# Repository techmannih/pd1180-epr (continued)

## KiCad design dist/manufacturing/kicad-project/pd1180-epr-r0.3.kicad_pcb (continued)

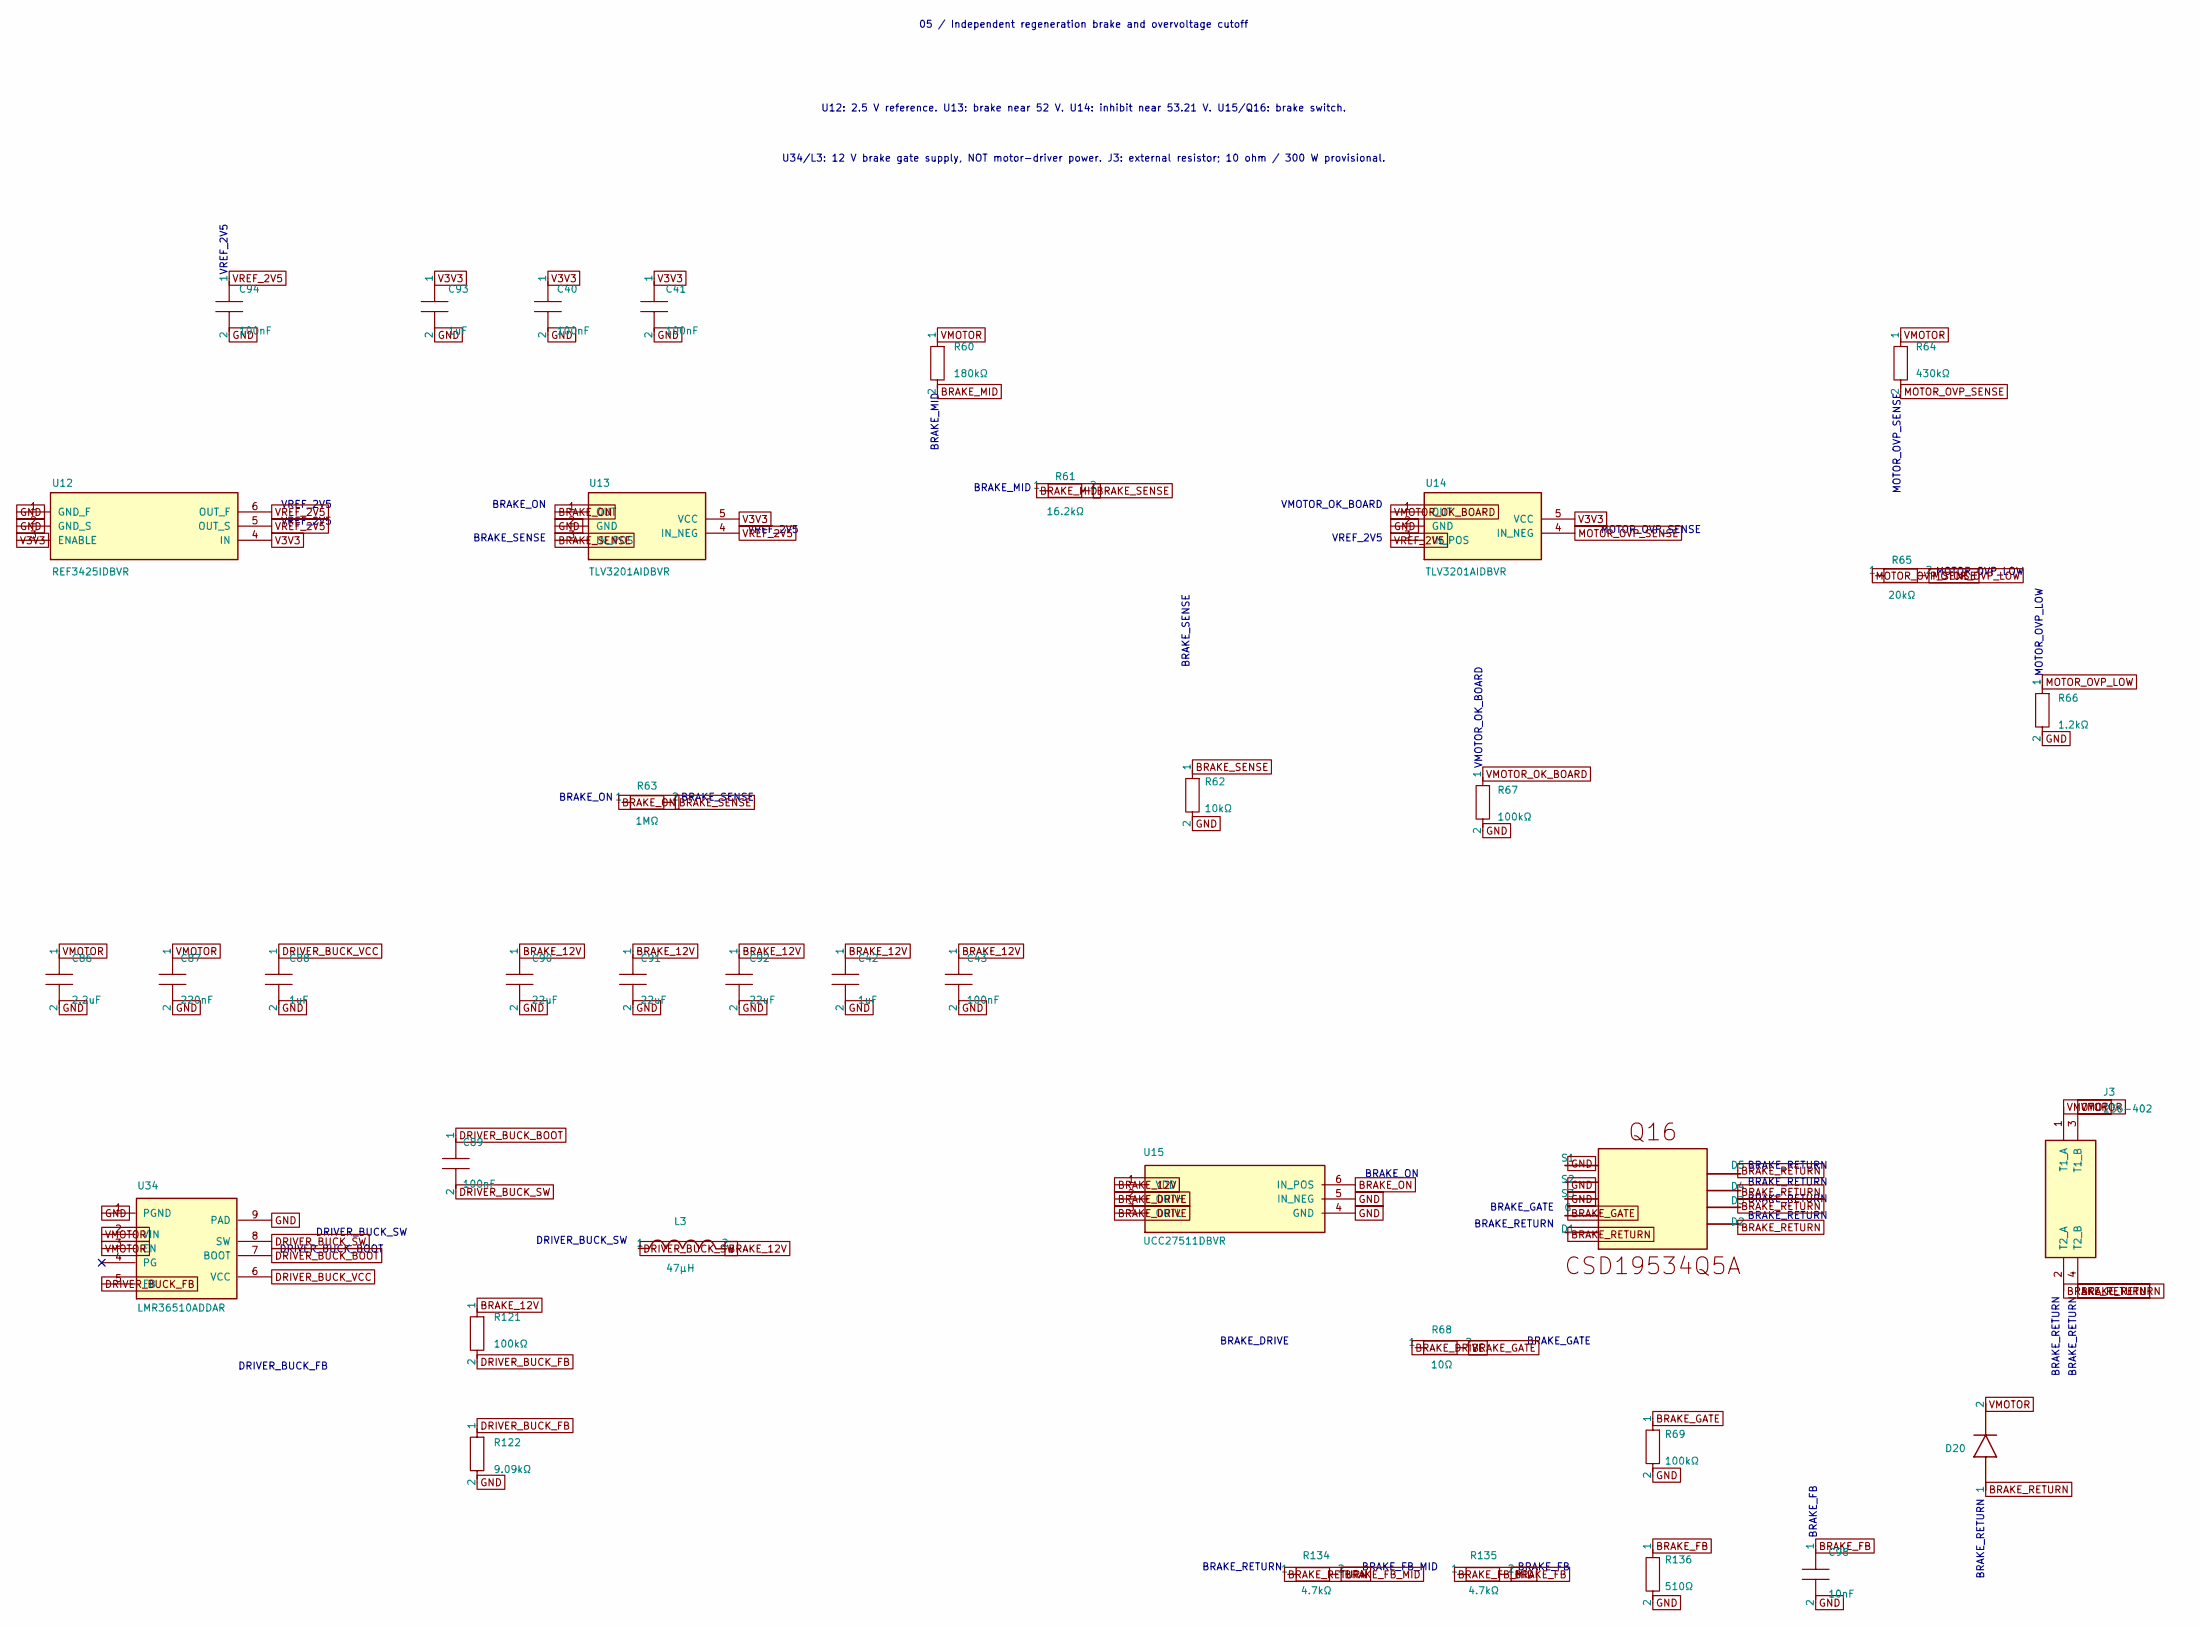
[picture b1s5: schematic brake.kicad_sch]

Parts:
C40, C41, C43, C89, C94: 100nF; capacitor_cap0603
C42, C88, C93: 1uF; capacitor_cap0603
C86: 2.2uF; capacitor_cap1206
C87: 220nF; capacitor_cap0805
C90, C91, C92: 22uF; capacitor_cap0805
C98: 10nF; capacitor_cap0603
D20: D; SS10100
J3: 236-402
L3: 47µH; SRP7050TA-470M
Q16: CSD19534Q5A
R60: 180kΩ; resistor_res0805
R61: 16.2kΩ; resistor_res0603
R62: 10kΩ; resistor_res0603
R63: 1MΩ; resistor_res0603
R64: 430kΩ; resistor_res0603
R65: 20kΩ; resistor_res0603
R66: 1.2kΩ; resistor_res0603
R67, R69, R121: 100kΩ; resistor_res0603
R68: 10Ω; resistor_res0603
R122: 9.09kΩ; resistor_res0603
R134, R135: 4.7kΩ; resistor_res1206
R136: 510Ω; resistor_res0603
U12: REF3425IDBVR
U13, U14: TLV3201AIDBVR
U15: UCC27511DBVR
U34: LMR36510ADDAR

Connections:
BRAKE_12V: C42.1, C43.1, C90.1, C91.1, C92.1, L3.2, R121.1, U15.1 (VDD)
BRAKE_DRIVE: R68.1, U15.2 (OUTH), U15.3 (OUTL)
BRAKE_FB: C98.1, R135.2, R136.1; also elsewhere on the board
BRAKE_FB_MID: R134.2, R135.1
BRAKE_GATE: Q16.4 (G), R68.2, R69.1
BRAKE_MID: R60.2, R61.1
BRAKE_ON: R63.1, U13.1 (OUT), U15.6 (IN_POS)
BRAKE_RETURN: D20.2 (1), J3.2 (T2_A), J3.4 (T2_B), Q16.5 (D1), Q16.6 (D2), Q16.7 (D3), Q16.8 (D4), Q16.9 (D5), R134.1
BRAKE_SENSE: R61.2, R62.1, R63.2, U13.3 (IN_POS)
DRIVER_BUCK_BOOT: C89.1, U34.7 (BOOT)
DRIVER_BUCK_FB: R121.2, R122.1, U34.5 (FB)
DRIVER_BUCK_SW: C89.2, L3.1, U34.8 (SW)
DRIVER_BUCK_VCC: C88.1, U34.6 (VCC)
GND: C40.2, C41.2, C42.2, C43.2, C86.2, C87.2, C88.2, C90.2, C91.2, C92.2, C93.2, C94.2, C98.2, Q16.1 (S1), Q16.2 (S2), Q16.3 (S3), R62.2, R66.2, R67.2, R69.2, R122.2, R136.2, U12.1 (GND_F), U12.2 (GND_S), U13.2 (GND), U14.2 (GND), U15.4 (GND), U15.5 (IN_NEG), U34.1 (PGND), U34.9 (PAD); also elsewhere on the board
MOTOR_OVP_LOW: R65.2, R66.1
MOTOR_OVP_SENSE: R64.2, R65.1, U14.4 (IN_NEG)
V3V3: C40.1, C41.1, C93.1, U12.3 (ENABLE), U12.4 (IN), U13.5 (VCC), U14.5 (VCC); also elsewhere on the board
VMOTOR: C86.1, C87.1, D20.1 (2), J3.1 (T1_A), J3.3 (T1_B), R60.1, R64.1, U34.2 (VIN), U34.3 (EN); also elsewhere on the board
VMOTOR_OK_BOARD: R67.1, U14.1 (OUT); also elsewhere on the board
VREF_2V5: C94.1, U12.5 (OUT_S), U12.6 (OUT_F), U13.4 (IN_NEG), U14.3 (IN_POS)

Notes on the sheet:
05 / Independent regeneration brake and overvoltage cutoff
U12: 2.5 V reference. U13: brake near 52 V. U14: inhibit near 53.21 V. U15/Q16: brake switch.
U34/L3: 12 V brake gate supply, NOT motor-driver power. J3: external resistor; 10 ohm / 300 W provisional.
DRIVER_BUCK_FB
DRIVER_BUCK_SW
VREF_2V5
BRAKE_ON
BRAKE_SENSE
MOTOR_OVP_SENSE
BRAKE_DRIVE
BRAKE_GATE
BRAKE_RETURN
BRAKE_FB
DRIVER_BUCK_BOOT
BRAKE_MID
VMOTOR_OK_BOARD
MOTOR_OVP_LOW
BRAKE_FB_MID

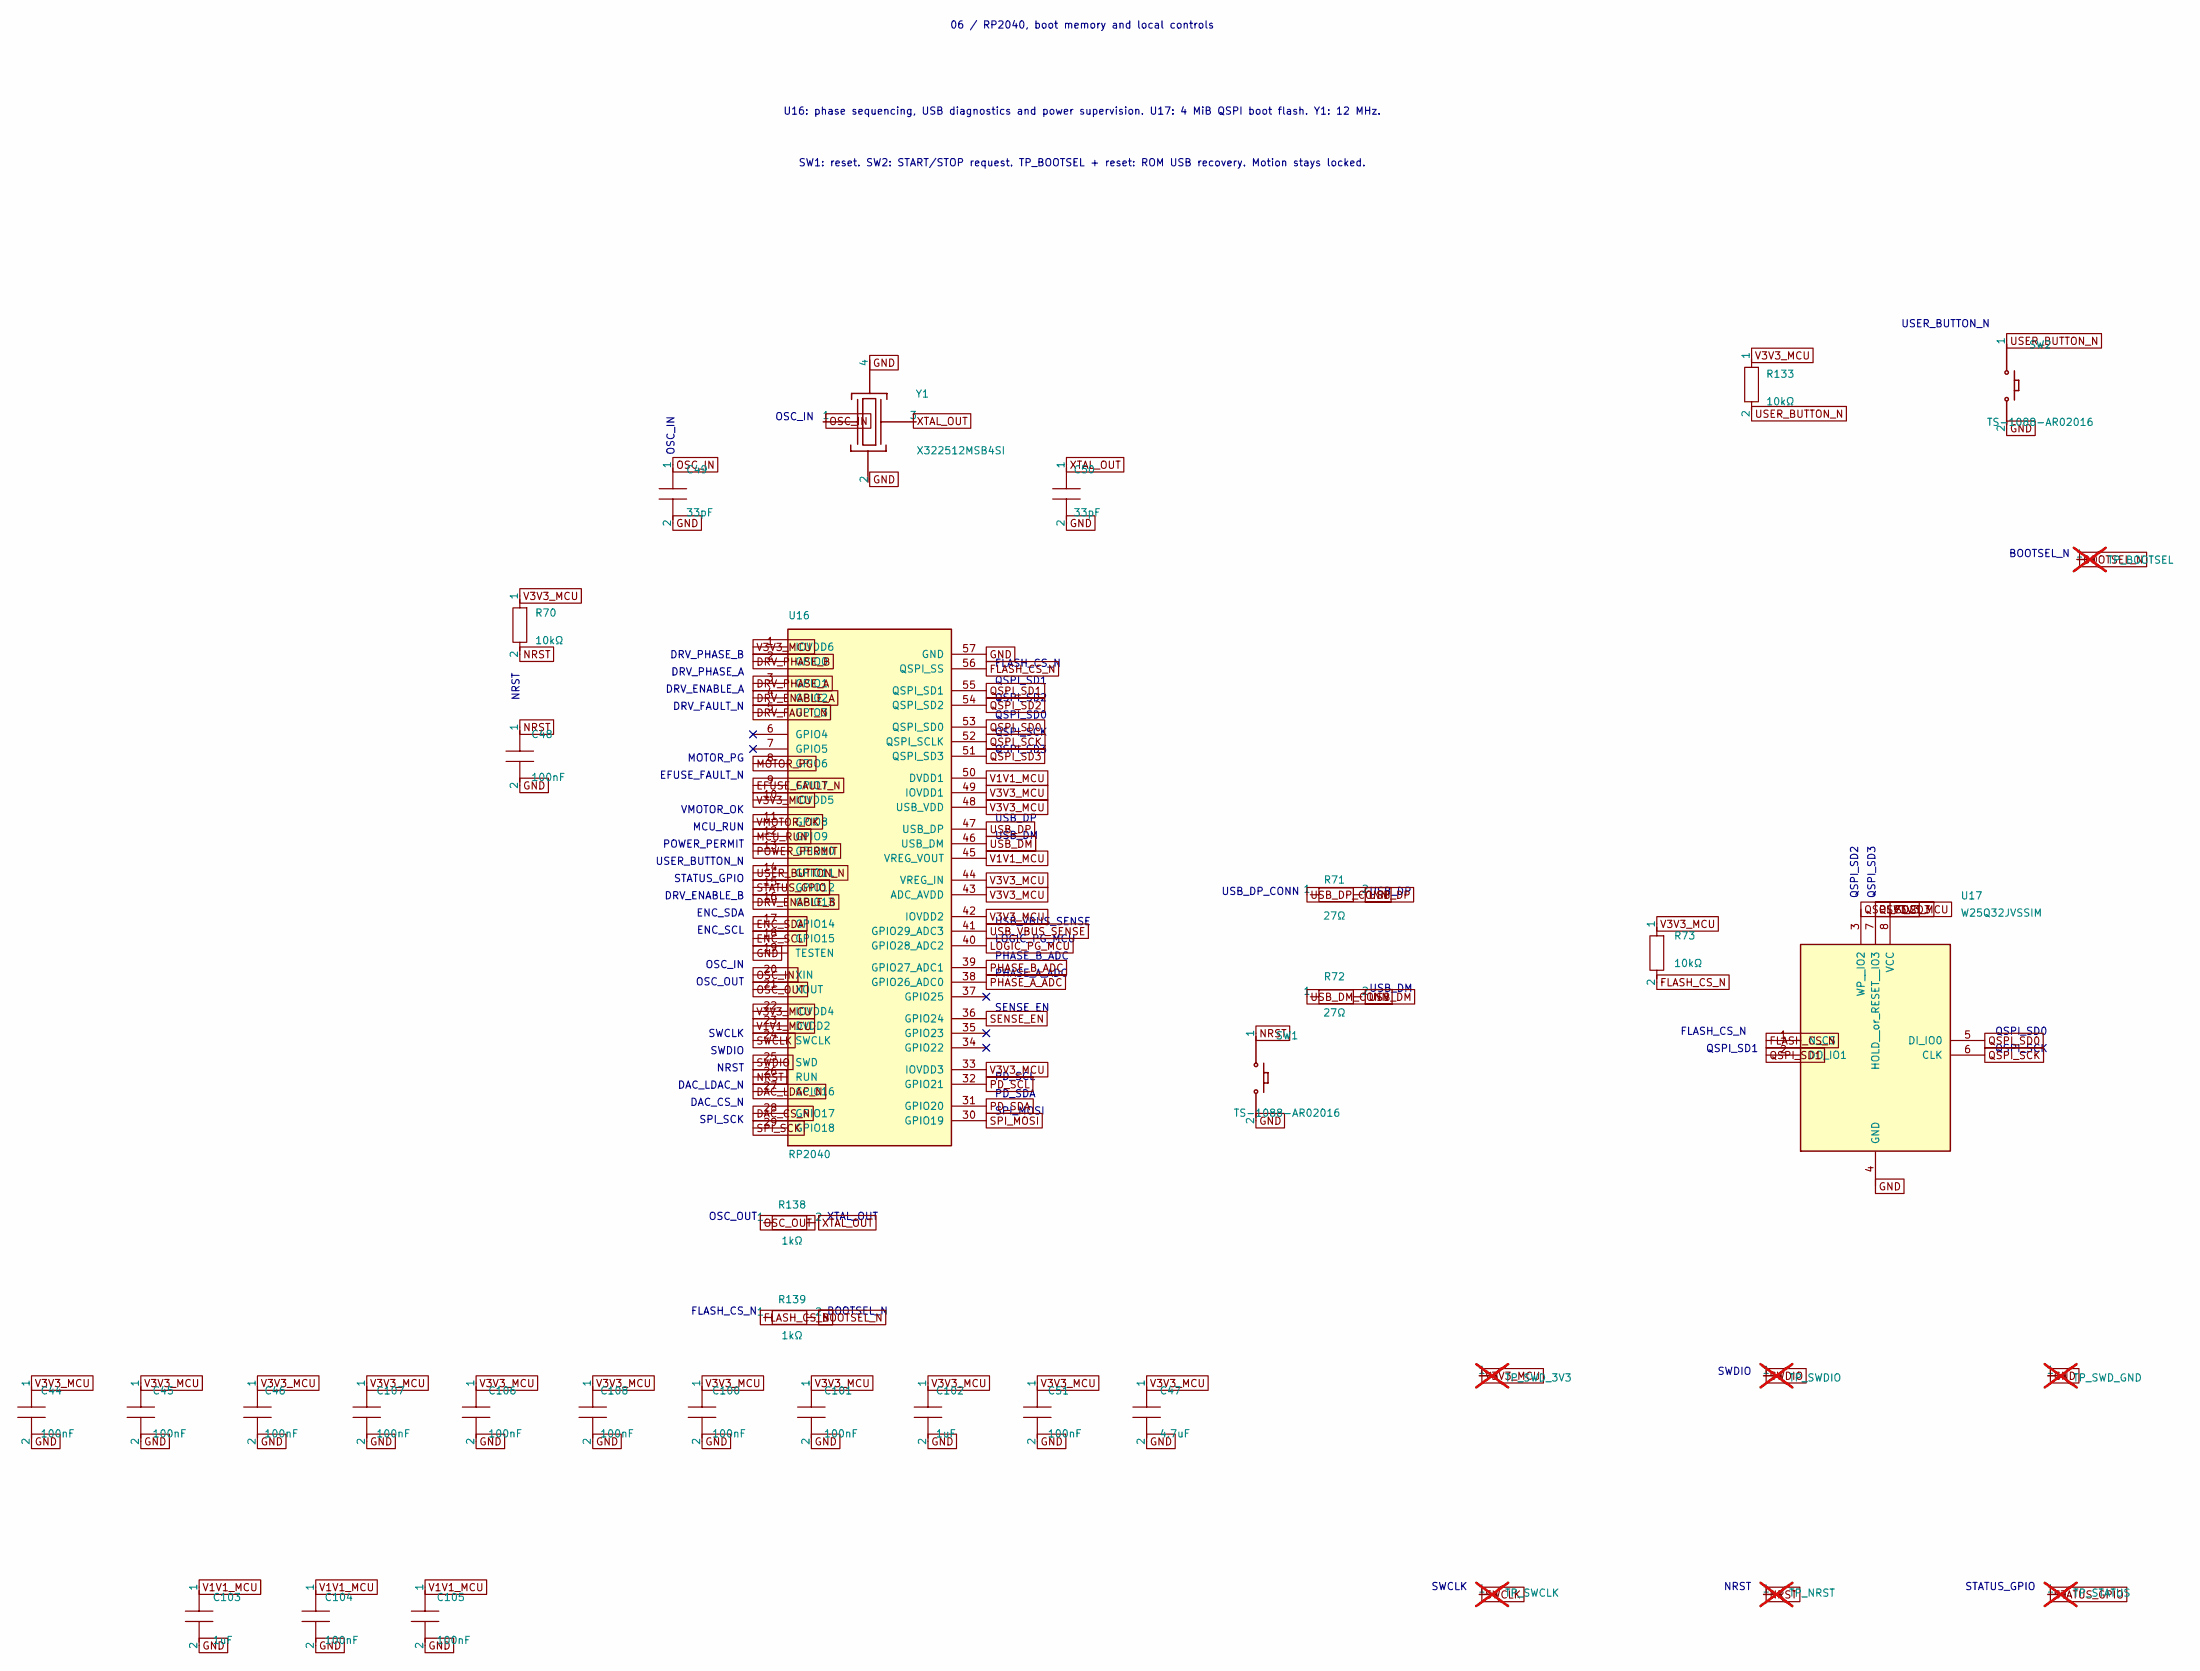
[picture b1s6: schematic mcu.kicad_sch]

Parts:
C44, C45, C46, C100, C101, C104, C105, C106, C107, C108: 100nF; capacitor_cap0402
C47: 4.7uF; capacitor_cap1206
C48, C51: 100nF; capacitor_cap0603
C49, C50: 33pF; capacitor_cap0603
C102, C103: 1uF; capacitor_cap0402
R70, R73, R133: 10kΩ; resistor_res0603
R71, R72: 27Ω; resistor_res0603
R138, R139: 1kΩ; resistor_res0603
SW1, SW2: TS-1088-AR02016
TP_BOOTSEL: TP_BOOTSEL; test_point; not fitted
TP_NRST: TP_NRST; test_point; not fitted
TP_STATUS: TP_STATUS; test_point; not fitted
TP_SWCLK: TP_SWCLK; test_point; not fitted
TP_SWDIO: TP_SWDIO; test_point; not fitted
TP_SWD_3V3: TP_SWD_3V3; test_point; not fitted
TP_SWD_GND: TP_SWD_GND; test_point; not fitted
U16: RP2040
U17: W25Q32JVSSIM
Y1: X322512MSB4SI

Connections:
BOOTSEL_N: R139.2, TP_BOOTSEL.1
DAC_CS_N: U16.28 (GPIO17); also elsewhere on the board
DAC_LDAC_N: U16.27 (GPIO16); also elsewhere on the board
DRV_ENABLE_A: U16.4 (GPIO2); also elsewhere on the board
DRV_ENABLE_B: U16.16 (GPIO13); also elsewhere on the board
DRV_FAULT_N: U16.5 (GPIO3); also elsewhere on the board
DRV_PHASE_A: U16.3 (GPIO1); also elsewhere on the board
DRV_PHASE_B: U16.2 (GPIO0); also elsewhere on the board
EFUSE_FAULT_N: U16.9 (GPIO7); also elsewhere on the board
ENC_SCL: U16.18 (GPIO15); also elsewhere on the board
ENC_SDA: U16.17 (GPIO14); also elsewhere on the board
FLASH_CS_N: R73.2, R139.1, U16.56 (QSPI_SS), U17.1 (N_CS)
GND: C44.2, C45.2, C46.2, C47.2, C48.2, C49.2, C50.2, C51.2, C100.2, C101.2, C102.2, C103.2, C104.2, C105.2, C106.2, C107.2, C108.2, SW1.2, SW2.2, TP_SWD_GND.1, U16.19 (TESTEN), U16.57 (GND), U17.4 (GND), Y1.2, Y1.4; also elsewhere on the board
LOGIC_PG_MCU: U16.40 (GPIO28_ADC2); also elsewhere on the board
MCU_RUN: U16.12 (GPIO9); also elsewhere on the board
MOTOR_PG: U16.8 (GPIO6); also elsewhere on the board
NRST: C48.1, R70.2, SW1.1, TP_NRST.1, U16.26 (RUN)
OSC_IN: C49.1, U16.20 (XIN), Y1.1
OSC_OUT: R138.1, U16.21 (XOUT)
PD_SCL: U16.32 (GPIO21); also elsewhere on the board
PD_SDA: U16.31 (GPIO20); also elsewhere on the board
PHASE_A_ADC: U16.38 (GPIO26_ADC0); also elsewhere on the board
PHASE_B_ADC: U16.39 (GPIO27_ADC1); also elsewhere on the board
POWER_PERMIT: U16.13 (GPIO10); also elsewhere on the board
QSPI_SCK: U16.52 (QSPI_SCLK), U17.6 (CLK)
QSPI_SD0: U16.53 (QSPI_SD0), U17.5 (DI_IO0)
QSPI_SD1: U16.55 (QSPI_SD1), U17.2 (DO_IO1)
QSPI_SD2: U16.54 (QSPI_SD2), U17.3 (WP__IO2)
QSPI_SD3: U16.51 (QSPI_SD3), U17.7 (HOLD__or_RESET__IO3)
SENSE_EN: U16.36 (GPIO24); also elsewhere on the board
SPI_MOSI: U16.30 (GPIO19); also elsewhere on the board
SPI_SCK: U16.29 (GPIO18); also elsewhere on the board
STATUS_GPIO: TP_STATUS.1, U16.15 (GPIO12); also elsewhere on the board
SWCLK: TP_SWCLK.1, U16.24 (SWCLK)
SWDIO: TP_SWDIO.1, U16.25 (SWD)
USB_DM: R72.2, U16.46 (USB_DM)
USB_DM_CONN: R72.1; also elsewhere on the board
USB_DP: R71.2, U16.47 (USB_DP)
USB_DP_CONN: R71.1; also elsewhere on the board
USB_VBUS_SENSE: U16.41 (GPIO29_ADC3); also elsewhere on the board
USER_BUTTON_N: R133.2, SW2.1, U16.14 (GPIO11)
V1V1_MCU: C103.1, C104.1, C105.1, U16.23 (DVDD2), U16.45 (VREG_VOUT), U16.50 (DVDD1)
V3V3_MCU: C44.1, C45.1, C46.1, C47.1, C51.1, C100.1, C101.1, C102.1, C106.1, C107.1, C108.1, R70.1, R73.1, R133.1, TP_SWD_3V3.1, U16.1 (IOVDD6), U16.10 (IOVDD5), U16.22 (IOVDD4), U16.33 (IOVDD3), U16.42 (IOVDD2), U16.43 (ADC_AVDD), U16.44 (VREG_IN), U16.48 (USB_VDD), U16.49 (IOVDD1), U17.8 (VCC); also elsewhere on the board
VMOTOR_OK: U16.11 (GPIO8); also elsewhere on the board
XTAL_OUT: C50.1, R138.2, Y1.3

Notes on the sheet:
06 / RP2040, boot memory and local controls
U16: phase sequencing, USB diagnostics and power supervision. U17: 4 MiB QSPI boot flash. Y1: 12 MHz.
SW1: reset. SW2: START/STOP request. TP_BOOTSEL + reset: ROM USB recovery. Motion stays locked.
OSC_OUT
FLASH_CS_N
USER_BUTTON_N
OSC_IN
NRST
XTAL_OUT
BOOTSEL_N
DRV_PHASE_B
DRV_PHASE_A
DRV_ENABLE_A
DRV_FAULT_N
MOTOR_PG
EFUSE_FAULT_N
VMOTOR_OK
MCU_RUN
POWER_PERMIT
STATUS_GPIO
DRV_ENABLE_B
ENC_SDA
ENC_SCL
SWCLK
SWDIO
DAC_LDAC_N
DAC_CS_N
SPI_SCK
SPI_MOSI
PD_SDA
PD_SCL
SENSE_EN
PHASE_A_ADC
PHASE_B_ADC
LOGIC_PG_MCU
USB_VBUS_SENSE
USB_DM
USB_DP
QSPI_SD3
QSPI_SCK

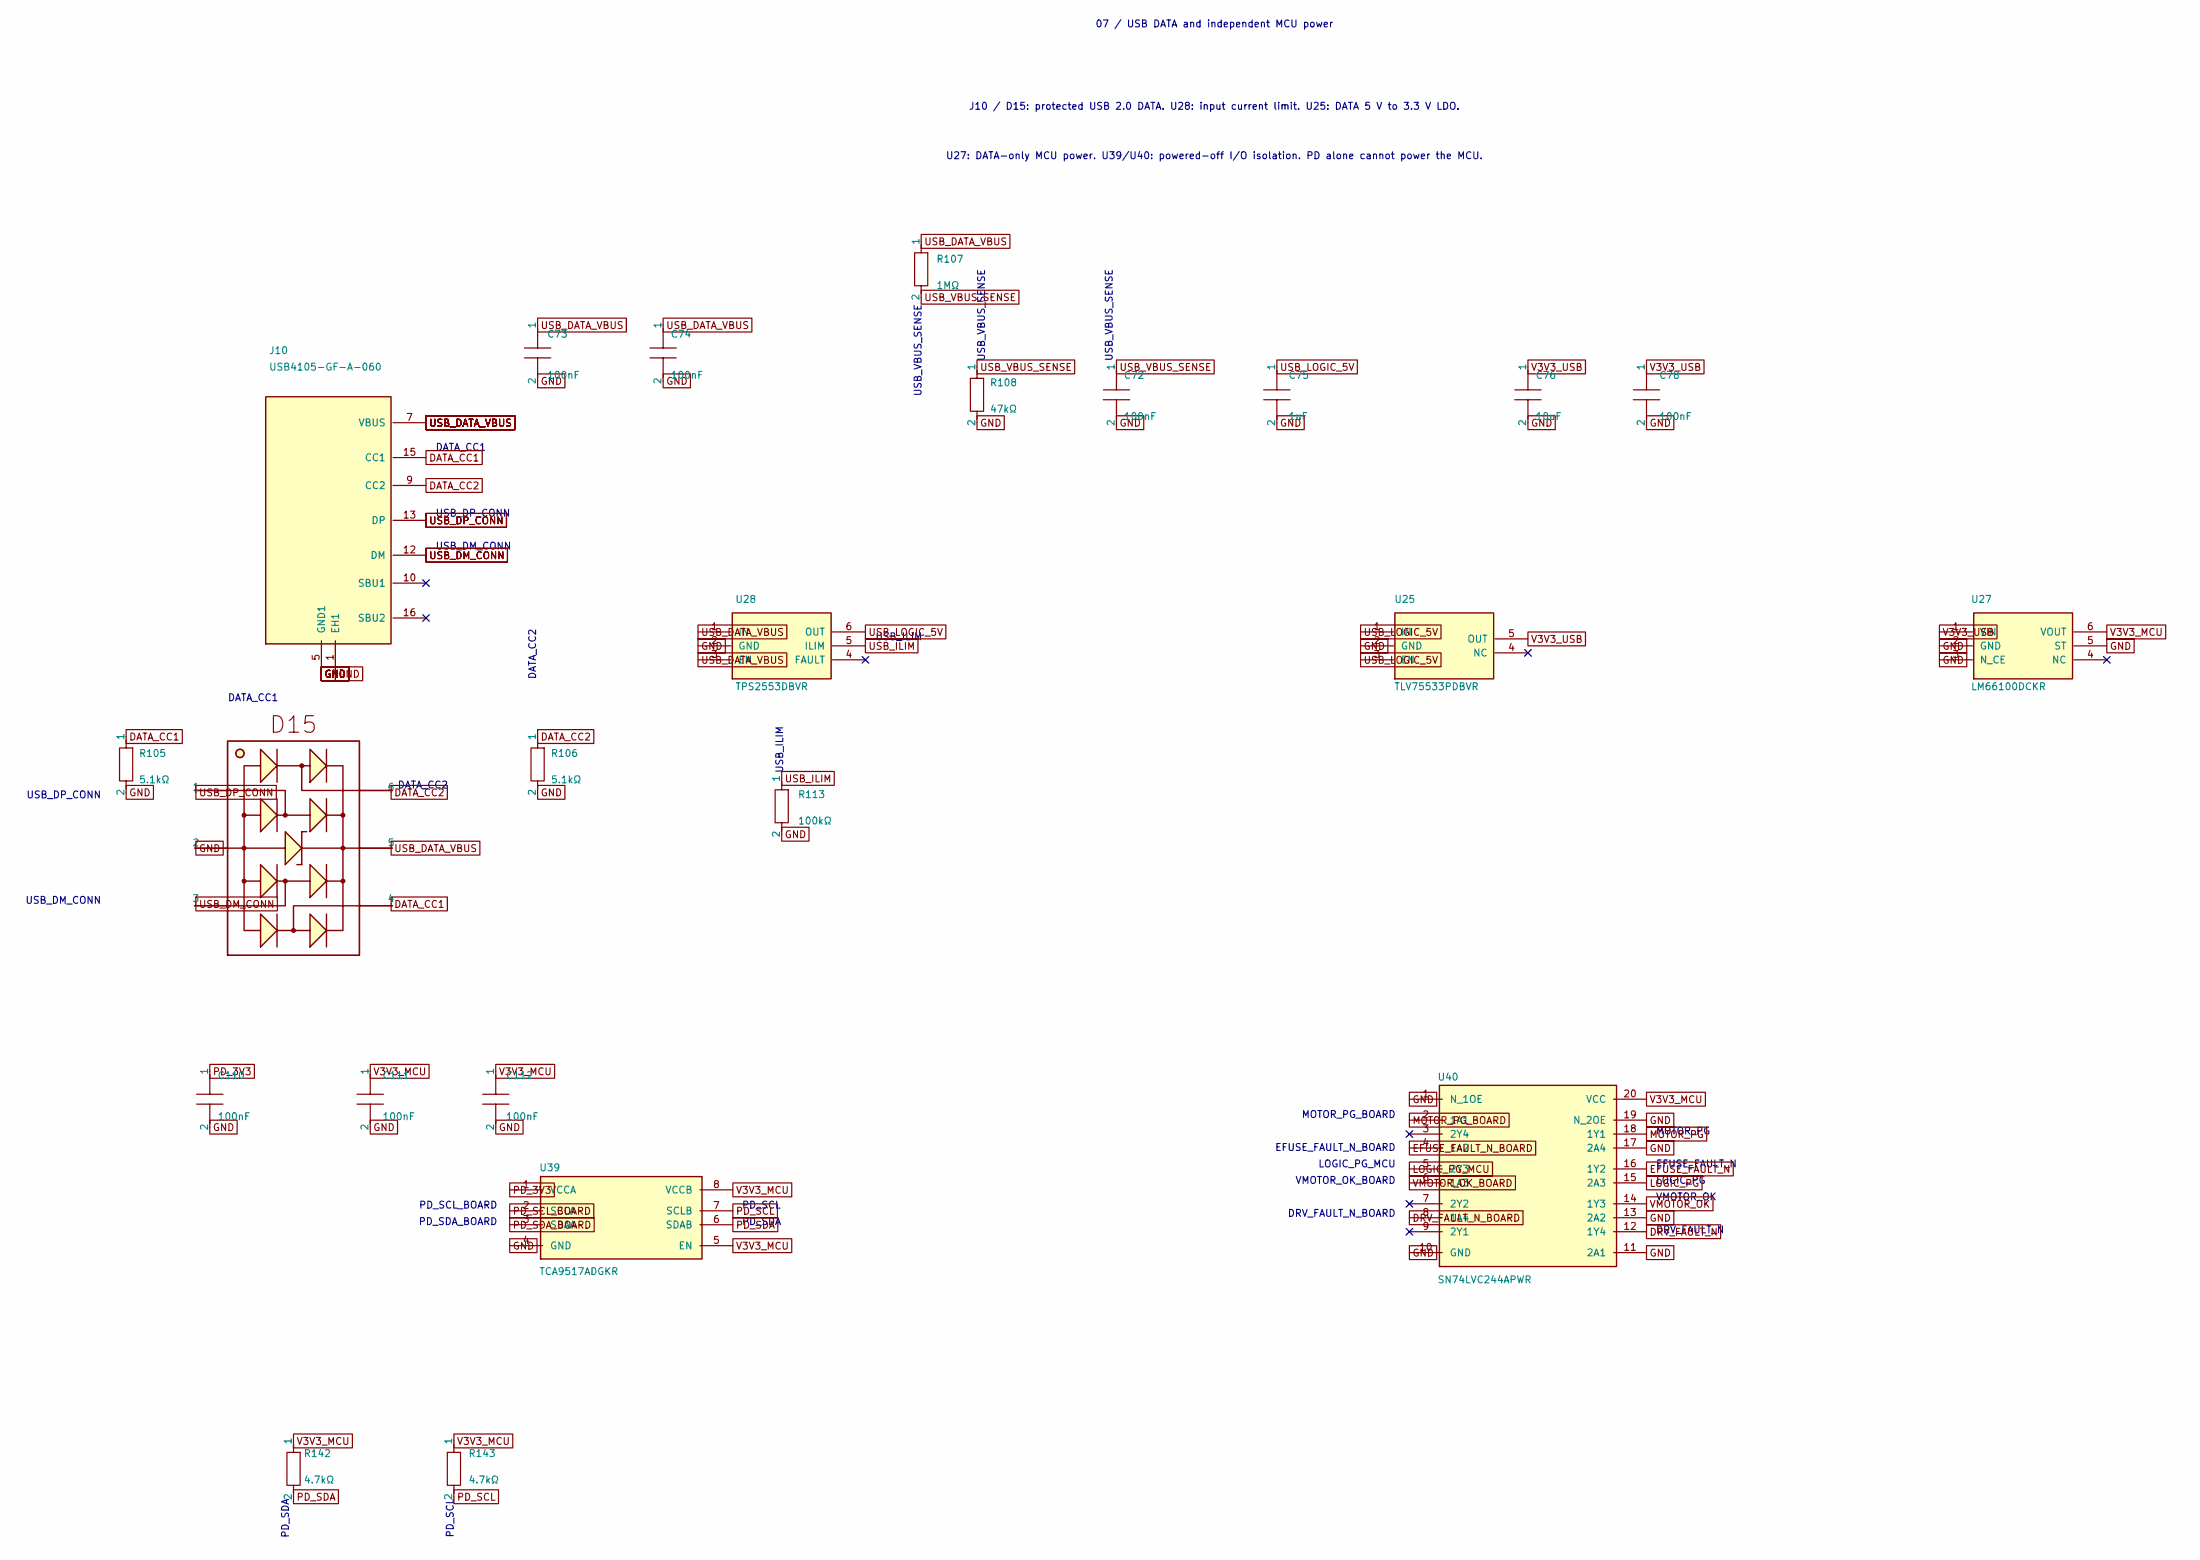
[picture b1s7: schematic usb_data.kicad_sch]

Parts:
C72, C73, C74, C78, C110, C111, C112: 100nF; capacitor_cap0603
C75: 1uF; capacitor_cap0603
C76: 10uF; capacitor_cap0603
D15: USBLC6-4SC6
J10: USB4105-GF-A-060
R105, R106: 5.1kΩ; resistor_res0603
R107: 1MΩ; resistor_res0603
R108: 47kΩ; resistor_res0603
R113: 100kΩ; resistor_res0603
R142, R143: 4.7kΩ; resistor_res0603
U25: TLV75533PDBVR
U27: LM66100DCKR
U28: TPS2553DBVR
U39: TCA9517ADGKR
U40: SN74LVC244APWR

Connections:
DATA_CC1: D15.4, J10.15 (CC1), R105.1
DATA_CC2: D15.6, J10.9 (CC2), R106.1
DRV_FAULT_N: U40.12 (1Y4); also elsewhere on the board
DRV_FAULT_N_BOARD: U40.8 (1A4); also elsewhere on the board
EFUSE_FAULT_N: U40.16 (1Y2); also elsewhere on the board
EFUSE_FAULT_N_BOARD: U40.4 (1A2); also elsewhere on the board
GND: C72.2, C73.2, C74.2, C75.2, C76.2, C78.2, C110.2, C111.2, C112.2, D15.2, J10.1 (EH1), J10.2 (GND1), J10.3 (GND1), J10.4 (GND1), J10.5 (GND1), J10.6 (GND1), J10.19 (GND1), J10.20 (GND1), R105.2, R106.2, R108.2, R113.2, U25.2 (GND), U27.2 (GND), U27.3 (N_CE), U27.5 (ST), U28.2 (GND), U39.4 (GND), U40.1 (N_1OE), U40.10 (GND), U40.11 (2A1), U40.13 (2A2), U40.17 (2A4), U40.19 (N_2OE); also elsewhere on the board
LOGIC_PG: U40.15 (2A3); also elsewhere on the board
LOGIC_PG_MCU: U40.5 (2Y3); also elsewhere on the board
MOTOR_PG: U40.18 (1Y1); also elsewhere on the board
MOTOR_PG_BOARD: U40.2 (1A1); also elsewhere on the board
PD_3V3: C110.1, U39.1 (VCCA); also elsewhere on the board
PD_SCL: R143.2, U39.7 (SCLB); also elsewhere on the board
PD_SCL_BOARD: U39.2 (SCLA); also elsewhere on the board
PD_SDA: R142.2, U39.6 (SDAB); also elsewhere on the board
PD_SDA_BOARD: U39.3 (SDAA); also elsewhere on the board
USB_DATA_VBUS: C73.1, C74.1, D15.5, J10.7 (VBUS), J10.8 (VBUS), J10.17 (VBUS), J10.18 (VBUS), R107.1, U28.1 (IN), U28.3 (EN)
USB_DM_CONN: D15.3, J10.12 (DM), J10.14 (DM); also elsewhere on the board
USB_DP_CONN: D15.1, J10.11 (DP), J10.13 (DP); also elsewhere on the board
USB_ILIM: R113.1, U28.5 (ILIM)
USB_LOGIC_5V: C75.1, U25.1 (IN), U25.3 (EN), U28.6 (OUT)
USB_VBUS_SENSE: C72.1, R107.2, R108.1; also elsewhere on the board
V3V3_MCU: C111.1, C112.1, R142.1, R143.1, U27.6 (VOUT), U39.5 (EN), U39.8 (VCCB), U40.20 (VCC); also elsewhere on the board
V3V3_USB: C76.1, C78.1, U25.5 (OUT), U27.1 (VIN)
VMOTOR_OK: U40.14 (1Y3); also elsewhere on the board
VMOTOR_OK_BOARD: U40.6 (1A3); also elsewhere on the board

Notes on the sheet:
07 / USB DATA and independent MCU power
J10 / D15: protected USB 2.0 DATA. U28: input current limit. U25: DATA 5 V to 3.3 V LDO.
U27: DATA-only MCU power. U39/U40: powered-off I/O isolation. PD alone cannot power the MCU.
USB_VBUS_SENSE
DATA_CC2
DATA_CC1
USB_DM_CONN
USB_DP_CONN
PD_SCL_BOARD
PD_SDA_BOARD
PD_SDA
PD_SCL
MOTOR_PG_BOARD
EFUSE_FAULT_N_BOARD
LOGIC_PG_MCU
VMOTOR_OK_BOARD
DRV_FAULT_N_BOARD
DRV_FAULT_N
VMOTOR_OK
LOGIC_PG
EFUSE_FAULT_N
MOTOR_PG
USB_ILIM

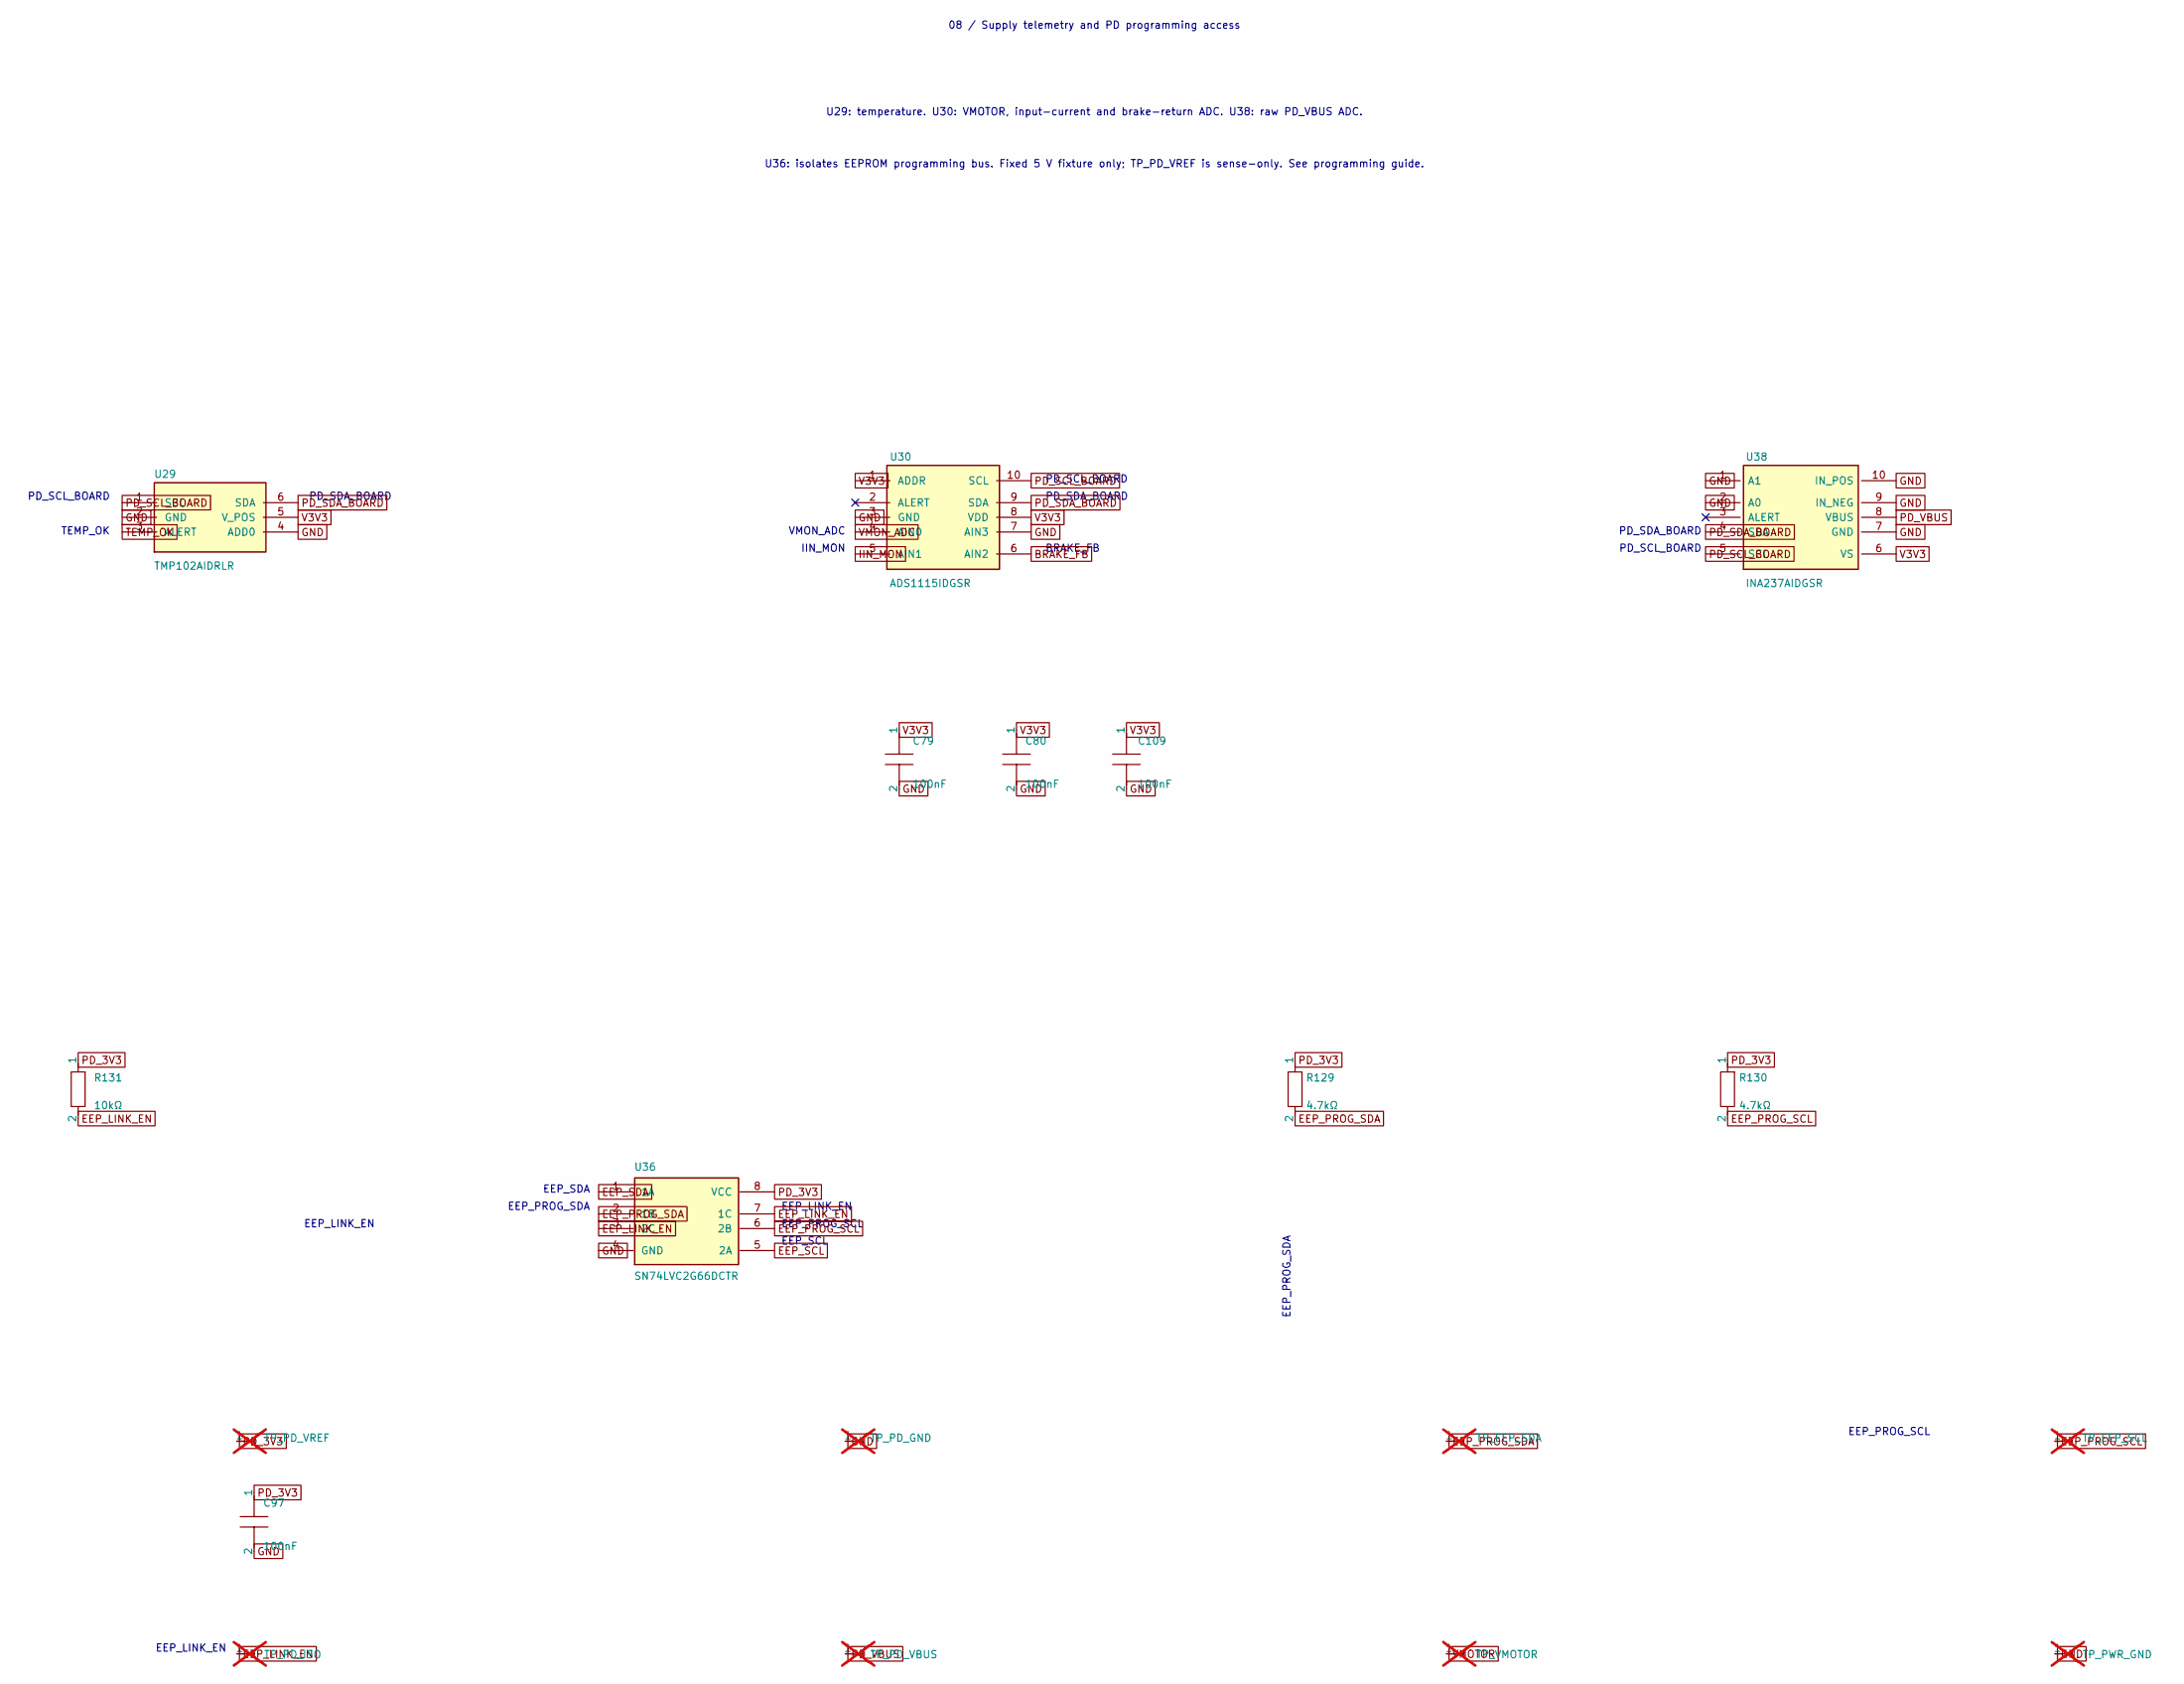
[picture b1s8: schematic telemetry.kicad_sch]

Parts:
C79, C80, C97, C109: 100nF; capacitor_cap0603
R129, R130: 4.7kΩ; resistor_res0603
R131: 10kΩ; resistor_res0603
TP_EEP_SCL: TP_EEP_SCL; test_point; not fitted
TP_EEP_SDA: TP_EEP_SDA; test_point; not fitted
TP_PD_GND: TP_PD_GND; test_point; not fitted
TP_PD_ISO: TP_PD_ISO; test_point; not fitted
TP_PD_VBUS: TP_PD_VBUS; test_point; not fitted
TP_PD_VREF: TP_PD_VREF; test_point; not fitted
TP_PWR_GND: TP_PWR_GND; test_point; not fitted
TP_VMOTOR: TP_VMOTOR; test_point; not fitted
U29: TMP102AIDRLR
U30: ADS1115IDGSR
U36: SN74LVC2G66DCTR
U38: INA237AIDGSR

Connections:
BRAKE_FB: U30.6 (AIN2); also elsewhere on the board
EEP_LINK_EN: R131.2, TP_PD_ISO.1, U36.3 (2C), U36.7 (1C)
EEP_PROG_SCL: R130.2, TP_EEP_SCL.1, U36.6 (2B); also elsewhere on the board
EEP_PROG_SDA: R129.2, TP_EEP_SDA.1, U36.2 (1B); also elsewhere on the board
EEP_SCL: U36.5 (2A); also elsewhere on the board
EEP_SDA: U36.1 (1A); also elsewhere on the board
GND: C79.2, C80.2, C97.2, C109.2, TP_PD_GND.1, TP_PWR_GND.1, U29.2 (GND), U29.4 (ADD0), U30.3 (GND), U30.7 (AIN3), U36.4 (GND), U38.1 (A1), U38.2 (A0), U38.7 (GND), U38.9 (IN_NEG), U38.10 (IN_POS); also elsewhere on the board
IIN_MON: U30.5 (AIN1); also elsewhere on the board
PD_3V3: C97.1, R129.1, R130.1, R131.1, TP_PD_VREF.1, U36.8 (VCC); also elsewhere on the board
PD_SCL_BOARD: U29.1 (SCL), U30.10 (SCL), U38.5 (SCL); also elsewhere on the board
PD_SDA_BOARD: U29.6 (SDA), U30.9 (SDA), U38.4 (SDA); also elsewhere on the board
PD_VBUS: TP_PD_VBUS.1, U38.8 (VBUS); also elsewhere on the board
TEMP_OK: U29.3 (ALERT); also elsewhere on the board
V3V3: C79.1, C80.1, C109.1, U29.5 (V_POS), U30.1 (ADDR), U30.8 (VDD), U38.6 (VS); also elsewhere on the board
VMON_ADC: U30.4 (AIN0); also elsewhere on the board
VMOTOR: TP_VMOTOR.1; also elsewhere on the board

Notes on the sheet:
08 / Supply telemetry and PD programming access
U29: temperature. U30: VMOTOR, input-current and brake-return ADC. U38: raw PD_VBUS ADC.
U36: isolates EEPROM programming bus. Fixed 5 V fixture only; TP_PD_VREF is sense-only. See programming guide.
PD_SCL_BOARD
PD_SDA_BOARD
EEP_PROG_SDA
EEP_LINK_EN
EEP_PROG_SCL
TEMP_OK
VMON_ADC
IIN_MON
BRAKE_FB
EEP_SDA
EEP_SCL

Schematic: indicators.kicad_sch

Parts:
BZ1: FMB09A03-3V
C52: 100nF; capacitor_cap0603; not fitted
C53: 1uF; capacitor_cap0603; not fitted
C95, C99: 100nF; capacitor_cap0603
C96: 10uF; capacitor_cap0603
C113: 1uF; capacitor_cap0603
D16: NH-B2020RGBA-HF
D17: XL-1608SURC-06
D18: D; BAV21W-7-F
Q26: AO3400A
R123, R126: 1kΩ; resistor_res0603
R124, R125: 330Ω; resistor_res0603
R127, R145: 100kΩ; resistor_res0603
R128, R140, R141: 4.7kΩ; resistor_res0603
R132: 10kΩ; resistor_res0603
R137: 47kΩ; resistor_res0603
TP_ENC_3V3: TP_ENC_3V3; test_point; not fitted
TP_ENC_A: TP_ENC_A; test_point; not fitted
TP_ENC_B: TP_ENC_B; test_point; not fitted
TP_ENC_GND: TP_ENC_GND; test_point; not fitted
TP_ENC_I: TP_ENC_I; test_point; not fitted
U18: AS5600-ASOM; not fitted
U35: PCA9538PWR
U37: SN74LVC1G17DBVR
U41: TPS22919DCKR

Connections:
BUZZER_EN: R126.1, U35.7 (P3)
BUZZER_GATE: Q26.1 (G), R126.2, R127.1
BUZZER_LOW: BZ1.2 (NEG), D18.2 (1), Q26.3 (D)
ENC_OUT: TP_ENC_I.1, U18.3 (OUT)
ENC_SCL: R141.2, TP_ENC_B.1, U18.7 (SCL); also elsewhere on the board
ENC_SDA: R140.2, TP_ENC_A.1, U18.6 (SDA); also elsewhere on the board
GND: C52.2, C53.2, C95.2, C96.2, C99.2, C113.2, D17.1 (2), Q26.2 (S), R127.2, R132.2, R137.2, R145.2, TP_ENC_GND.1, U18.4 (GND), U18.8 (DIR), U35.1 (A0), U35.2 (A1), U35.8 (GND), U35.9 (P4), U35.10 (P5), U35.11 (P6), U35.12 (P7), U37.3 (GND), U41.2 (GND); also elsewhere on the board
PD_3V3: C95.1, C99.1, U35.16 (VCC), U37.5 (VCC); also elsewhere on the board
PD_SCL_BOARD: U35.14 (SCL); also elsewhere on the board
PD_SDA_BOARD: U35.15 (SDA); also elsewhere on the board
POWER_LED_A: D17.2 (1), R128.2
RGB_B_DRV: R125.2, U35.6 (P2)
RGB_B_K: D16.2 (B_K), R125.1
RGB_G_DRV: R124.2, U35.5 (P1)
RGB_G_K: D16.4 (G_K), R124.1
RGB_R_DRV: R123.2, U35.4 (P0)
RGB_R_K: D16.1 (R_K), R123.1
SENSE_EN: R145.1, U41.3 (ON); also elsewhere on the board
STATUS_GPIO: R132.1, U37.2 (A); also elsewhere on the board
U35_RESET_N: R137.1, U35.3 (N_RESET), U37.4 (Y)
V3V3: BZ1.1 (POS), C96.1, D16.3 (A), D18.1 (2), R128.1; also elsewhere on the board
V3V3_MCU: C113.1, U41.1 (IN); also elsewhere on the board
V3V3_SENS: C52.1, C53.1, R140.1, R141.1, TP_ENC_3V3.1, U18.1 (VDD5V), U18.2 (VDD3V3), U41.5 (QOD), U41.6 (VOUT); also elsewhere on the board

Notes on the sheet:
09 / Indicators, alarm and optional encoder
U35: RGB / buzzer I2C outputs. U37: reset-domain buffer. Q26: buzzer switch. D17: board-power LED.
U41: switched DATA-powered sensors. U18 AS5600 + C52/C53: DNP; no qualified rear magnet / closed-loop control.
ENC_SDA
ENC_SCL
U35_RESET_N
BUZZER_LOW
BUZZER_GATE
ENC_OUT
SENSE_EN
RGB_R_DRV
RGB_G_DRV
RGB_B_DRV
BUZZER_EN
PD_SCL_BOARD
PD_SDA_BOARD
STATUS_GPIO
RGB_R_K
RGB_G_K
RGB_B_K
